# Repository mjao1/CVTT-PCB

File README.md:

# CVTT-PCB
**Custom Embedded PCB for a Computer Vision-Based Table Tennis Robotic System**

<div align="center">

</div>

<div align="center">
<em>The dragon on the silkscreen references Ma Long, the goat of table tennis; 'Long (龍)' translates to 'dragon' from Mandarin.</em>
</div>

## Core Components

- **Microcontrollers and Compute:**
  - STM32G0B1RET6
  - Raspberry Pi Zero 2 W

## Actuation System

- **Motor Driver Support:**
  - 2 Brushless DC motors for flywheels
  - 2 Servos for direction and distance control
  - 1 Stepper motor for ball feeding

## Power and Regulation

- **Power Circuitry:**
  - 12V input
  - E-fuse circuit
  - 12V to 5V LDO Regulator
  - 5V to 3.3V LDO Regulator

## User Interface

- **Controls and Feedback:**
  - Manual/CV mode switch
  - LCD screen for manual control
  - LCD navigation buttons
  - Diagnostic LEDs
 
## STM32G0B1RET6 Pinout

### Inputs
| Signal        | Pin   |
|---------------|-------|
| UART_RX       | PB7   |
| LCD_MISO      | PD5   |
| LCD_BUTTONC   | PC4   |
| LCD_BUTTOND   | PC5   |
| LCD_BUTTONU   | PA7   |
| CV_MODE       | PB10  |
| PB13          | PB13  |

### Outputs
| Signal      | Pin  | Signal      | Pin  | Signal      | Pin  | Signal      | Pin  |
|-------------|------|-------------|------|-------------|------|-------------|------|
| UART_TX     | PB6  | LED_G       | PC6  | DRV_EN      | PA0  | LED_R       | PA9  |
| LCD_RESET   | PD2  | PWMB        | PC7  | DRV_STEP    | PA1  | LED_B       | PA10 |
| LCD_LED     | PD3  | STBY        | PC8  | DRV_DIR     | PA2  | LCD_CS      | PA15 |
| LCD_DC/RS   | PD4  | PWMA        | PC11 | BIN2        | PA3  | SERVO1_PWM  | PB0  |
| LCD_MOSI    | PD6  | DRV_SLEEP   | PD8  | BIN1        | PA4  | SERVO2_PWM  | PB1  |
| LCD_SCK     | PB3  | DRV_RST     | PD9  | AIN1        | PA5  | EFUSE_EN    | PB14 |
|             |      |             |      | AIN2        | PA6  |             |      |

### Tag
| Signal  | Pin   |
|---------|-------|
| SWDIO   | PA13  |
| SWKCLK  | PA14  |

## RPI Zero 2 W Pinout

### Inputs
| Signal              | Pin    |
|---------------------|--------|
| SC1174 input        | —      |
| UART_TX             | GPIO15 |

### Outputs
| Signal  | Pin    |
|---------|--------|
| UART_RX | GPIO14 |

## Next Steps
- Programming STM machine logic state machine
  - Design LCD user interface for manual and vision modes
- Programming RPI CV player recognition algorithm
  - Using RPI AI camera (SC1174) for inference acceleration

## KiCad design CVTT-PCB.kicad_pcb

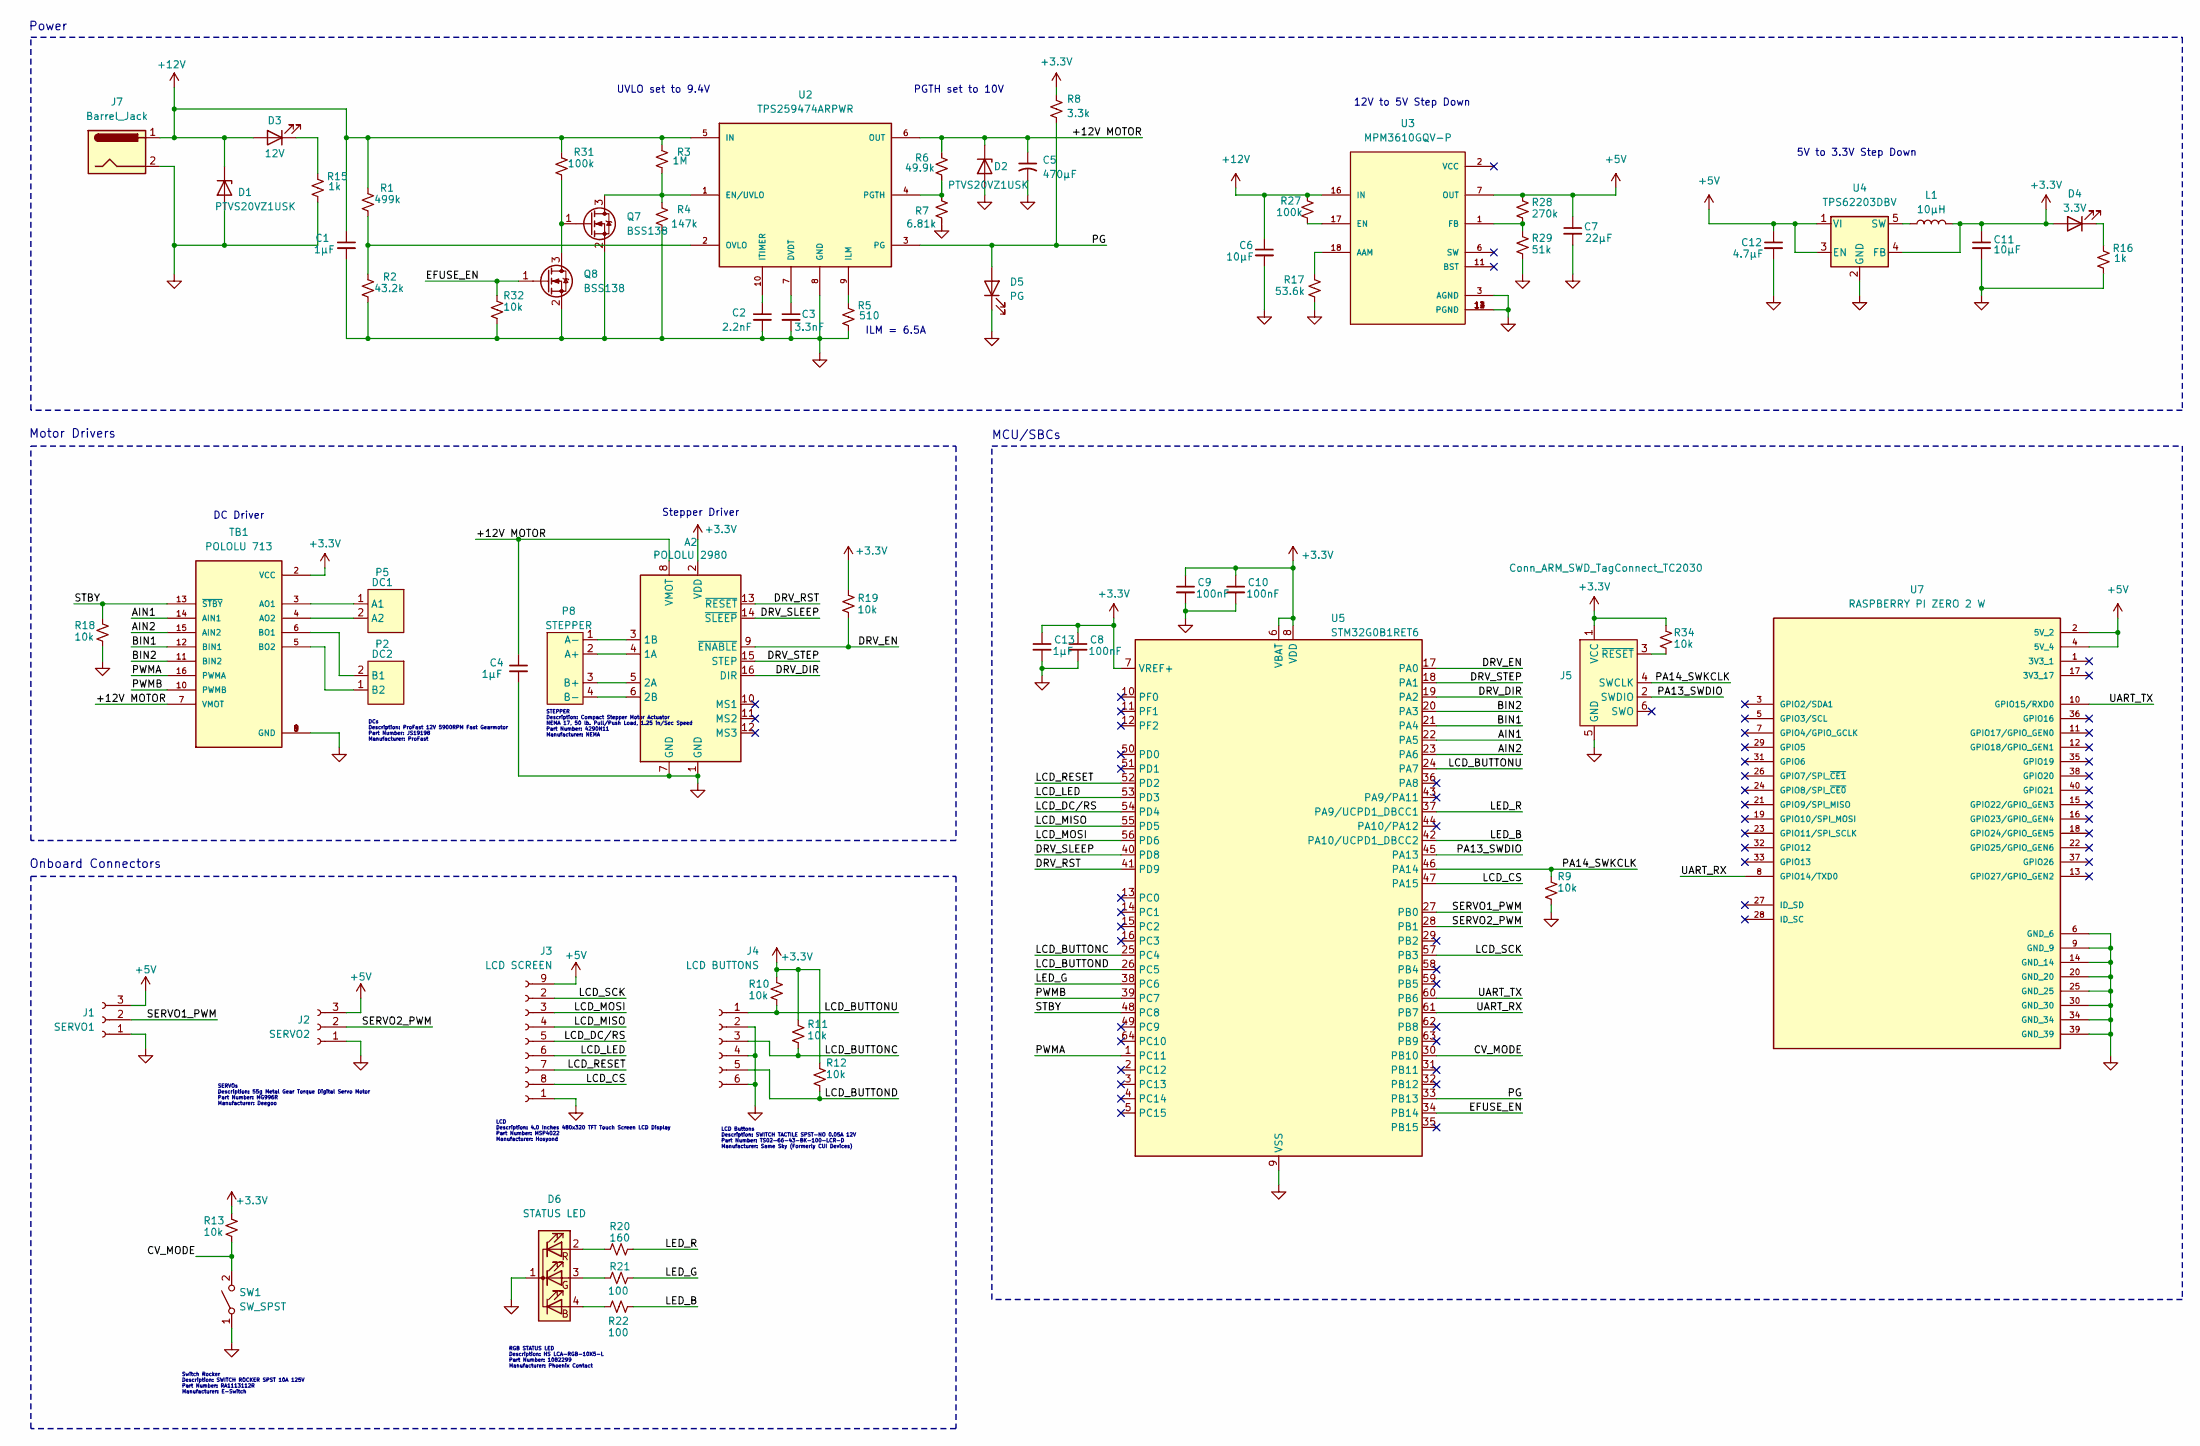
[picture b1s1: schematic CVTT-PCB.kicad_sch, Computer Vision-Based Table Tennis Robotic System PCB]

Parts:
A2: POLOLU 2980; Pololu_Breakout-16_15.2x20.3mm; Part Number A4988
C1, C4, C13: 1µF; C_0603_1608Metric_Pad1.08x0.95mm_HandSolder; Part Number C0603C105Z3VACTU
C2: 2.2nF; C_0805_2012Metric_Pad1.18x1.45mm_HandSolder; Part Number C0805C222K3GECTU
C3: 3.3nF; C_0805_2012Metric_Pad1.18x1.45mm_HandSolder; Part Number C0805C332F5GECAUTO7210
C5: 470µF; UD_10X10_; Part Number UUD1E471MNL1GS
C6, C11: 10µF; C_0603_1608Metric_Pad1.08x0.95mm_HandSolder; Part Number GRM188R61E106KA73D
C7: 22µF; C_0603_1608Metric_Pad1.08x0.95mm_HandSolder; Part Number CL10A226MO7JZNC
C8, C9, C10: 100nF; C_0603_1608Metric_Pad1.08x0.95mm_HandSolder; Part Number C0603C105Z3VACTU
C12: 4.7µF; C_0603_1608Metric_Pad1.08x0.95mm_HandSolder; Part Number CL10A475KO8NNNC
D1, D2: PTVS20VZ1USK; Nexperia_DSN1608-2_1.6x0.8mm; Part Number PTVS20VZ1USK
D3: 12V; LED_0603_1608Metric; Part Number 150060BS75000
D4: 3.3V; LED_0603_1608Metric; Part Number 150060BS75000
D5: PG; LED_0603_1608Metric; Part Number 150060BS75000
D6: STATUS LED; PinHeader_1x04_P2.54mm_Vertical
J1: SERVO1; PinHeader_1x03_P2.54mm_Vertical
J2: SERVO2; PinHeader_1x03_P2.54mm_Vertical
J3: LCD SCREEN; PinHeader_1x09_P2.54mm_Vertical
J4: LCD BUTTONS; PinHeader_1x06_P2.54mm_Vertical
J5: Conn_ARM_SWD_TagConnect_TC2030; Tag-Connect_TC2030-IDC-FP_2x03_P1.27mm_Vertical
J7: Barrel_Jack; CUI_PJ-002B; Part Number PJ-002B
L1: 10µH; L_Bourns_SRU5016_5.2x5.2mm; Part Number SRU5016-100Y
P2: DC2; TerminalBlock_Phoenix_PT-1,5-2-3.5-H_1x02_P3.50mm_Horizontal
P5: DC1; TerminalBlock_Phoenix_PT-1,5-2-3.5-H_1x02_P3.50mm_Horizontal
P8: STEPPER; PinHeader_1x04_P2.54mm_Vertical; Part Number PH1-04-UA
Q7, Q8: BSS138; SOT-23-3; Part Number BSS138LT3G
R1: 499k; R_0603_1608Metric_Pad0.98x0.95mm_HandSolder; Part Number AF0603FR-07499KL
R2: 43.2k; R_0603_1608Metric_Pad0.98x0.95mm_HandSolder; Part Number RMCF0603FT43K2
R3: 1M; R_0603_1608Metric_Pad0.98x0.95mm_HandSolder; Part Number ERJ-3EKF1004V
R4: 147k; R_0603_1608Metric_Pad0.98x0.95mm_HandSolder; Part Number RMCF0603FT147K
R5: 510; R_0603_1608Metric_Pad0.98x0.95mm_HandSolder; Part Number RC0603FR-07510RL
R6: 49.9k; R_0603_1608Metric_Pad0.98x0.95mm_HandSolder; Part Number RMEF0603FT49K9
R7: 6.81k; R_0603_1608Metric_Pad0.98x0.95mm_HandSolder; Part Number RC0603FR-076K81L
R8: 3.3k; R_0603_1608Metric_Pad0.98x0.95mm_HandSolder; Part Number RMCF0603JT3K30
R9, R10, R11, R12, R13, R18, R19, R32, R34: 10k; R_0603_1608Metric_Pad0.98x0.95mm_HandSolder; Part Number CRCW060310K0FKEE
R15, R16: 1k; R_0603_1608Metric_Pad0.98x0.95mm_HandSolder; Part Number RCS06031K00FKEA
R17: 53.6k; R_0603_1608Metric_Pad0.98x0.95mm_HandSolder; Part Number CRCW060353K6FKEAC
R20: 160; R_0603_1608Metric_Pad0.98x0.95mm_HandSolder; Part Number CRCW060310K0FKEE
R21, R22: 100; R_0603_1608Metric_Pad0.98x0.95mm_HandSolder; Part Number CRCW060310K0FKEE
R27, R31: 100k; R_0603_1608Metric_Pad0.98x0.95mm_HandSolder; Part Number RCS0603100KFKEA
R28: 270k; R_0603_1608Metric_Pad0.98x0.95mm_HandSolder; Part Number RC0603FR-07270KL
R29: 51k; R_0603_1608Metric_Pad0.98x0.95mm_HandSolder; Part Number RC0603FR-1351KL
SW1: SW_SPST; PinHeader_1x02_P2.54mm_Vertical; Part Number SWITCH ROCKER SPST 10A 125V
TB1: POLOLU 713; SHIELD_POLOLU-713; Part Number TB6612FNG
U2: TPS259474ARPWR; IC_TPS25974ARPWR; PARTREV A
U3: MPM3610GQV-P; CONV_MPM3610GQV-P; PARTREV 1.01
U4: TPS62203DBV; SOT-23-5; Part Number TPS62203DBVT
U5: STM32G0B1RET6; LQFP-64_10x10mm_P0.5mm; Part Number STM32G0B1RET6
U7: RASPBERRY PI ZERO 2 W; MODULE_RASPBERRY_PI_ZERO_2_W; PARTREV April 2024

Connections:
+3.3V: A2.2 (VDD), C8.1, C9.1, C10.1, C11.1, C13.1, D4.2 (A), J5.1 (VCC), L1.2, R8.1, R10.1, R11.1, R12.1, R13.1, R19.1, R34.1, TB1.2 (VCC), U4.4 (FB), U5.6 (VBAT), U5.7 (VREF+), U5.8 (VDD)
+5V: C7.1, C12.1, J1.3 (Pin_1), J2.3 (Pin_1), J3.9 (Pin_1), R28.1, U3.7 (OUT), U4.1 (VI), U4.3 (EN), U7.2 (5V_2), U7.4 (5V_4)
+12V: C1.1, C6.1, D1.1 (K), D3.2 (A), J7.1, R1.1, R3.1, R27.1, R31.1, U2.5 (IN), U3.16 (IN)
/+12V MOTOR: A2.8 (VMOT), C4.1, C5.1, D2.1 (K), R6.1, TB1.7 (VMOT), U2.6 (OUT)
/AIN1: TB1.14 (AIN1), U5.22 (PA5)
/AIN2: TB1.15 (AIN2), U5.23 (PA6)
/BIN1: TB1.12 (BIN1), U5.21 (PA4)
/BIN2: TB1.11 (BIN2), U5.20 (PA3)
/CV_MODE: R13.2, SW1.2 (B), U5.30 (PB10)
/DRV_DIR: A2.16 (DIR), U5.19 (PA2)
/DRV_EN: A2.9 (~ENABLE), R19.2, U5.17 (PA0)
/DRV_RST: A2.13 (~RESET), U5.41 (PD9)
/DRV_SLEEP: A2.14 (~SLEEP), U5.40 (PD8)
/DRV_STEP: A2.15 (STEP), U5.18 (PA1)
/EFUSE_EN: Q8.1 (G), R32.1, U5.34 (PB14)
/LCD_BUTTONC: J4.3, R11.2, U5.25 (PC4)
/LCD_BUTTOND: J4.5, R12.2, U5.26 (PC5)
/LCD_BUTTONU: J4.1, R10.2, U5.24 (PA7)
/LCD_CS: J3.8, U5.47 (PA15)
/LCD_DC/RS: J3.5, U5.54 (PD4)
/LCD_LED: J3.6, U5.53 (PD3)
/LCD_MISO: J3.4, U5.55 (PD5)
/LCD_MOSI: J3.3, U5.56 (PD6)
/LCD_RESET: J3.7, U5.52 (PD2)
/LCD_SCK: J3.2, U5.57 (PB3)
/LED_B: R22.2, U5.42 (PA10/UCPD1_DBCC2)
/LED_G: R21.2, U5.38 (PC6)
/LED_R: R20.2, U5.37 (PA9/UCPD1_DBCC1)
/PA13_SWDIO: J5.2 (SWDIO), U5.45 (PA13)
/PA14_SWKCLK: J5.4 (SWCLK), R9.1, U5.46 (PA14)
/PG: D5.2 (A), R8.2, U2.3 (PG), U5.33 (PB13)
/PWMA: TB1.16 (PWMA), U5.1 (PC11)
/PWMB: TB1.10 (PWMB), U5.39 (PC7)
/SERVO1_PWM: J1.2, U5.27 (PB0)
/SERVO2_PWM: J2.2, U5.28 (PB1)
/STBY: R18.1, TB1.13 (~STBY), U5.48 (PC8)
/UART_RX: U5.61 (PB7), U7.8 (GPIO14/TXD0)
/UART_TX: U5.60 (PB6), U7.10 (GPIO15/RXD0)
GND: A2.1 (GND), A2.7 (GND), C1.2, C2.2, C3.2, C4.2, C5.2, C6.2, C7.2, C8.2, C9.2, C10.2, C11.2, C12.2, C13.2, D1.2 (A), D2.2 (A), D5.1 (K), D6.1 (K), J1.1 (Pin_3), J2.1 (Pin_3), J3.1 (Pin_9), J4.2, J4.4, J4.6, J5.5 (GND), J7.2, Q7.2 (S), Q8.2 (S), R2.2, R4.2, R5.2, R7.2, R9.2, R15.2, R16.2, R17.2, R18.2, R29.2, R32.2, SW1.1 (A), TB1.1 (GND), TB1.8 (GND), TB1.9 (GND), U2.8 (GND), U3.3 (AGND), U3.12 (PGND), U3.13 (PGND), U3.14 (PGND), U4.2 (GND), U5.9 (VSS), U7.6 (GND_6), U7.9 (GND_9), U7.14 (GND_14), U7.20 (GND_20), U7.25 (GND_25), U7.30 (GND_30), U7.34 (GND_34), U7.39 (GND_39)
unnamed: A2.4 (1A), P8.2 (A+)
unnamed: A2.3 (1B), P8.1 (A-)
unnamed: A2.5 (2A), P8.3 (B+)
unnamed: A2.6 (2B), P8.4 (B-)
unnamed: D3.1 (K), R15.1
unnamed: D4.1 (K), R16.1
unnamed: D6.4 (BA), R22.1
unnamed: D6.3 (GA), R21.1
unnamed: D6.2 (RA), R20.1
unnamed: J5.3 (~RESET), R34.2
unnamed: P2.2 (B1), TB1.6 (BO1)
unnamed: P2.1 (B2), TB1.5 (BO2)
unnamed: P5.1 (A1), TB1.3 (AO1)
unnamed: P5.2 (A2), TB1.4 (AO2)
unnamed: Q7.3 (D), R3.2, R4.1, U2.1 (EN/UVLO)
unnamed: Q7.1 (G), Q8.3 (D), R31.2
unnamed: C3.1, U2.7 (DVDT)
unnamed: R5.1, U2.9 (ILM)
unnamed: C2.1, U2.10 (ITIMER)
unnamed: R1.2, R2.1, U2.2 (OVLO)
unnamed: R6.2, R7.1, U2.4 (PGTH)
unnamed: R17.1, U3.18 (AAM)
unnamed: R27.2, U3.17 (EN)
unnamed: R28.2, R29.1, U3.1 (FB)
unnamed: L1.1, U4.5 (SW)

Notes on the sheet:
MCU/SBCs
STEPPER Description: Compact Stepper Motor Actuator NEMA 17, 50 lb. Pull/Push Load, 1.25 in/Sec Speed Part Number: 4290N11 Manufacturer: NEMA
RGB STATUS LED Description: HS LCA-RGB-10X5-L Part Number: 1082299 Manufacturer: Phoenix Contact
UVLO set to 9.4V
Switch Rocker Description: SWITCH ROCKER SPST 10A 125V Part Number: RA1113112R Manufacturer: E-Switch
Motor Drivers
PGTH set to 10V
SERVOs Description: 55g Metal Gear Torque Digital Servo Motor Part Number: MG996R Manufacturer: Deegoo
ILM = 6.5A
5V to 3.3V Step Down
LCD Buttons Description: SWITCH TACTILE SPST-NO 0.05A 12V Part Number: TS02-66-43-BK-100-LCR-D Manufacturer: Same Sky (Formerly CUI Devices)
Stepper Driver
DCs Description: ProFast 12V 5900RPM Fast Gearmotor Part Number: JS19198 Manufacturer: ProFast
Power
LCD Description: 4.0 Inches 480x320 TFT Touch Screen LCD Display Part Number: MSP4022 Manufacturer: Hosyond
Onboard Connectors
DC Driver
12V to 5V Step Down

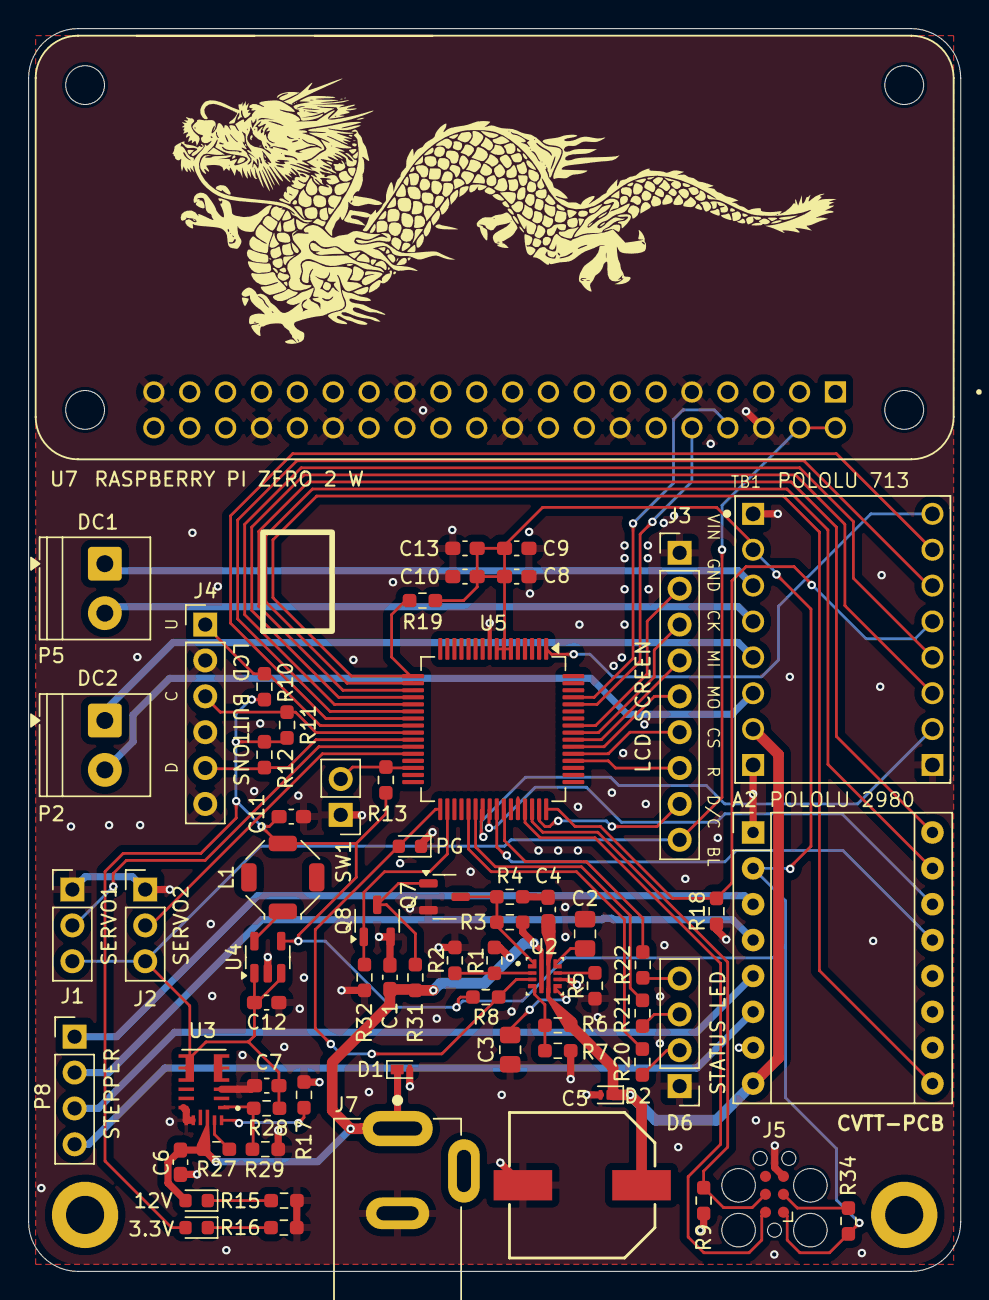
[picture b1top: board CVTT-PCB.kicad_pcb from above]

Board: 4 copper layers, 66.0 x 88.0 mm, 66 parts (0 on the bottom side), 64 nets.

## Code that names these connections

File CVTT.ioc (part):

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Mcu.Name=STM32G0B1R(B-C-E)Tx
Mcu.Package=LQFP64
Mcu.UserName=STM32G0B1RETx
PA0.Signal=GPIO_Output
PA1.Signal=GPIO_Output
PA10.Signal=GPIO_Output
PA13.Mode=Serial_Wire
PA13.Signal=SYS_SWDIO
PA14-BOOT0.Mode=Serial_Wire
PA14-BOOT0.Signal=SYS_SWCLK
PA15.Mode=NSS_Signal_Hard_Output
PA15.Signal=SPI1_NSS
PA2.Signal=GPIO_Output
PA3.Signal=GPIO_Output
PA4.Signal=GPIO_Output
PA5.Signal=GPIO_Output
PA6.Signal=GPIO_Output
PA7.Signal=GPIO_Input
PA9.Signal=GPIO_Output
PB0.Signal=S_TIM3_CH3
PB1.Signal=S_TIM3_CH4
PB10.Signal=GPIO_Input
PB13.Signal=GPIO_Input
PB14.Signal=GPIO_Output
PB3.Mode=Full_Duplex_Master
PB3.Signal=SPI1_SCK
PB6.Mode=Asynchronous
PB6.Signal=USART1_TX
PB7.Mode=Asynchronous
PB7.Signal=USART1_RX
PC11.Signal=S_TIM1_CH4
PC4.Signal=GPIO_Input
PC5.Signal=GPIO_Input
PC6.Signal=GPIO_Output
PC7.Signal=S_TIM2_CH4
PC8.Signal=GPIO_Output
PD2.Signal=GPIO_Output
PD3.Signal=GPIO_Output
PD4.Signal=GPIO_Output
PD5.Mode=Full_Duplex_Master
PD5.Signal=SPI1_MISO
PD6.Mode=Full_Duplex_Master
PD6.Signal=SPI1_MOSI
PD8.Signal=GPIO_Output
PD9.Signal=GPIO_Output
PF0-OSC_IN\ (PF0).Mode=HSE-External-Oscillator
PF0-OSC_IN\ (PF0).Signal=RCC_OSC_IN
PF1-OSC_OUT\ (PF1).Mode=HSE-External-Oscillator
PF1-OSC_OUT\ (PF1).Signal=RCC_OSC_OUT
RCC.HSE_VALUE=8000000
RCC.SYSCLKFreq_VALUE=60000000
RCC.SYSCLKSource=RCC_SYSCLKSOURCE_PLLCLK
board=custom

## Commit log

2025-07-22 Add LED indicators
2025-07-25 Update schem and layout
2025-07-25 add images
2025-07-25 Update pinout
2025-07-26 add RGB led status indicator
2025-07-26 update assets
2025-07-26 update paths
2025-07-26 update layout
2025-07-26 remove misc
2025-07-27 usb replacement
2025-07-27 update mx config
2025-07-27 update sch
2025-07-27 update mx
2025-07-31 update layout labeling
2025-08-02 fix MPM3610GQV-P resistors
2025-08-02 remove pg led
2025-08-06 new pg
2025-08-07 reconfigure ILM for motor req
2025-08-10 resolve DRC errors
2025-08-10 final check before gerbers
2025-08-10 pg placement
2025-08-15 update sch info
2025-08-19 edit sch
2025-08-23 edit pcb
2025-09-09 Add PCBA image
2025-09-27 add base firmware
2025-09-29 relocate firmware files
